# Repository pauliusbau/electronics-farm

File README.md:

# electronics-farm
*All my personal electronics projects goes here..*

### TARDIS Pulsing Light

This is quick and simple TARDIS toy modification based on ATTiny85 uC and a SW-18020P vibration sensor.  More info can be found [here](https://github.com/pauliusbau/electronics-farm/tree/master/TARDIS)

### Flip-Dot Clock

Flip-Dot Clock - a clock made from flip-dot matrix usually used in public buses. Controller is based on ATMega16/32 uC and DS1307 RTC. Clock is also equipped with HC05 Bluetooth module for easy wireless time/date [synchronization](https://github.com/pauliusbau/raspberrypi-mayhem/tree/master/RPI-bluetoothTimeSynch).  

### LEDCtrl - LED Strip Controller

Overly engineered LED strip controller with PIR and LDR sensors based on ATMega8 uC. Firmware allows used to set all of the parameters through LCD menu. Also there is a lot of different working modes.

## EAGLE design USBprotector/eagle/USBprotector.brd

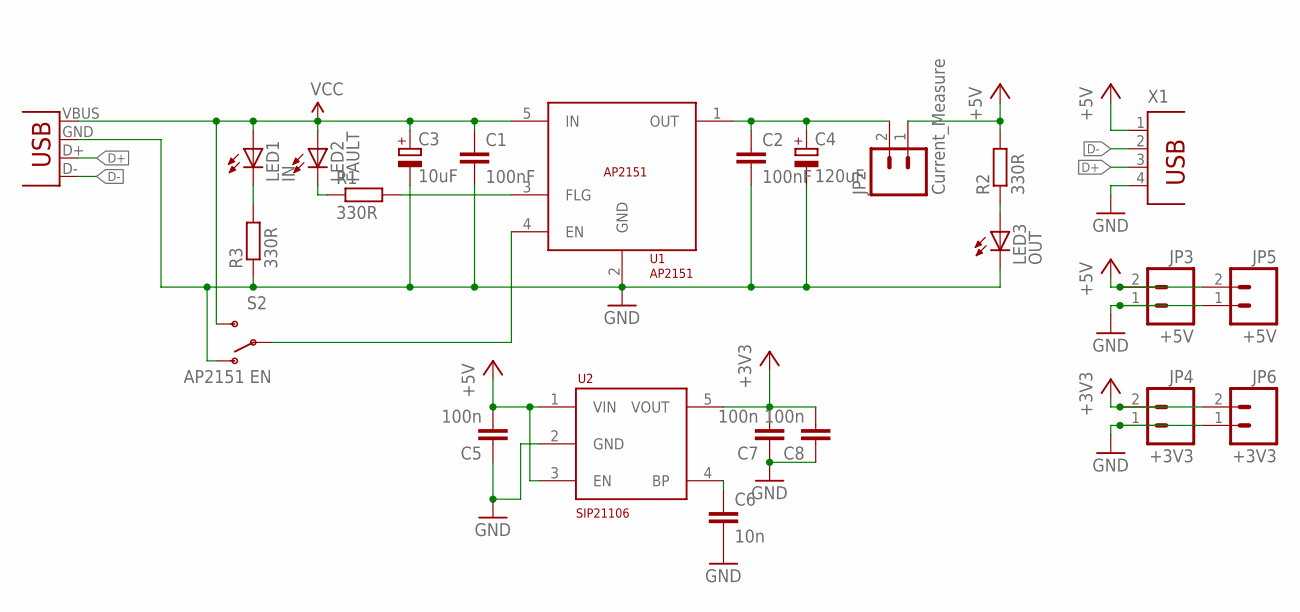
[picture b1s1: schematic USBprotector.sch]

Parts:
C1, C2: 100nF; C0805
C3: 10uF; SMC_C
C4: 120uF; SMC_C
C5, C8: 100n; C0805
C6: 10n; C0805
C7: 100n; C0603
JP1: USB-A-H
JP2: Current_Measure; 1X02
JP3: +5V; SCREWTERMINAL-3.5MM-2
JP4: +3V3; SCREWTERMINAL-3.5MM-2
JP5: +5V; MOLEX-1X2_LOCK
JP6: +3V3; MOLEX-1X2_LOCK
LED1: IN; LED3MM
LED2: FAULT; LED3MM
LED3: OUT; LED3MM
R1, R2, R3: 330R; R1206
S2: AP2151 EN; SWITCH-SPDT
U1: AP2151; SOT23-5
U2: SIP21106; SOT23-5
X1: PN87520

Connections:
5V_OUT: C2.1, C4.+, JP2.2, U1.1 (OUT)
+3V3: C7.2, C8.2, JP4.2, JP6.2, U2.5 (VOUT)
+5V: C5.2, JP2.1, JP3.2, JP5.2, R2.2, U2.1 (VIN), U2.3 (EN), X1.1
D+: JP1.D+ (D-), X1.3
D-: JP1.D- (D+), X1.2
EN: S2.2, U1.4 (EN)
FAULT: R1.2, U1.3 (FLG)
GND: C1.2, C2.2, C3.-, C4.-, C5.1, C6.2, C7.1, C8.1, JP1.GND (VBUS), JP3.1, JP4.1, JP5.1, JP6.1, LED3.K (C), R3.1, S2.1 (O), U1.2 (GND), U2.2 (GND), X1.4
unnamed: LED3.A, R2.1
unnamed: LED2.K (C), R1.1
unnamed: C6.1, U2.4 (BP)
unnamed: LED1.K (C), R3.2
VCC: C1.1, C3.+, JP1.VBUS (GND), LED1.A, LED2.A, S2.3 (S), U1.5 (IN)

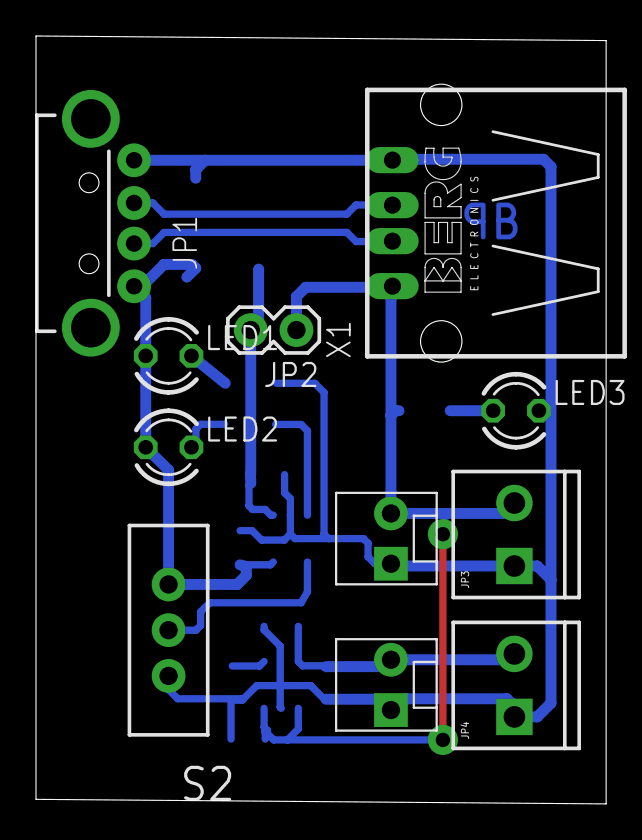
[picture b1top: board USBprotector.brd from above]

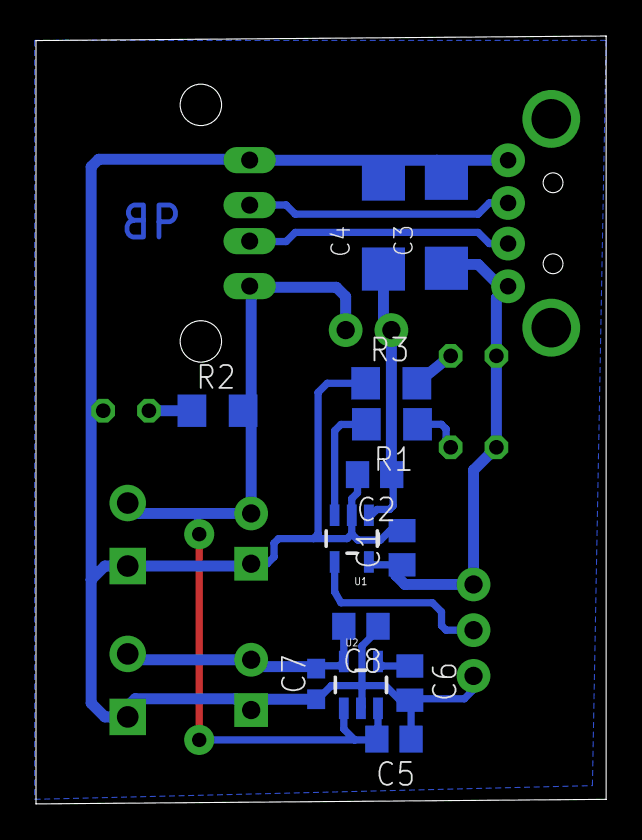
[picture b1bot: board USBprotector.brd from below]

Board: 2 copper layers, 31.7 x 42.7 mm, 24 parts (13 on the bottom side), 13 nets.

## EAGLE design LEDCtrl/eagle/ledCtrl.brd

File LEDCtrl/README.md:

# LEDCtrl - LED strip controller

#### More info and photos can be found in my Lithuanian blog: http://paulius.bautrenas.lt/blog/?p=227

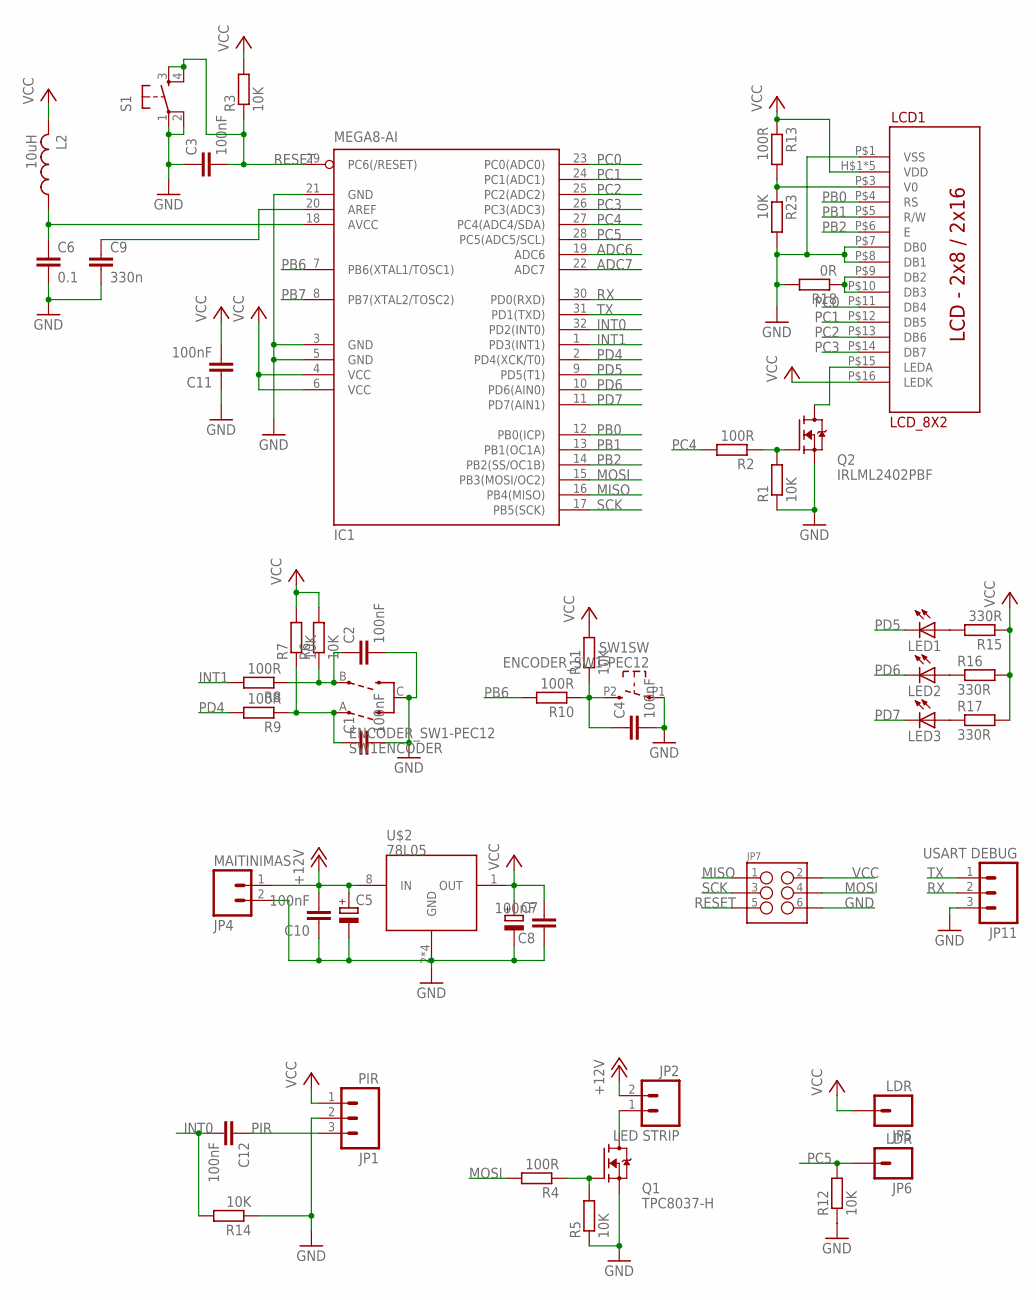
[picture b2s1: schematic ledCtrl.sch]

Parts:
C1, C2, C3, C4, C8, C10, C11, C12: 100nF; C0805
C5, C7: CPOL-EUSMCC; SMC_C
C6: 0.1; C0805K
C9: 330n; C0805
IC1: MEGA8-AI; TQFP32-08
JP1: PIR; 1X03_LOCK
JP2: LED STRIP; SCREWTERMINAL-3.5MM-2-NS
JP4: MAITINIMAS; SCREWTERMINAL-3.5MM-2-NS
JP5, JP6: LDR; 1X01_LONGPAD
JP7: M03X2; 2X3-SHROUDED
JP11: USART DEBUG; 1X03_LOCK
L2: 10uH; L2825P
LCD1: LCD_8X2; LCD_2X8
LED1, LED2, LED3: LEDCHIP-LED0805; CHIP-LED0805
Q1: TPC8037-H; SO8
Q2: IRLML2402PBF; SOT23
R1, R3, R5, R6, R7, R11, R14, R23: 10K; M0805
R2, R4, R8, R9, R10, R13: 100R; M0805
R12: 10K; M1206
R15, R16, R17: 330R; M0805
R18: 0R; M1206
S1: TAC_SWITCHPTH; TACTILE-PTH
SW1: ENCODER_SW1-PEC12; PEC12_INCREMENTAL_ENCODER
U$2: 78L05; SO8

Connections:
+12V: C5.+, C10.2, JP2.2, JP4.1, U$2.8 (IN)
ADC6: IC1.19 (ADC6)
ADC7: IC1.22 (ADC7)
AREF: C9.1, IC1.20 (AREF)
AVCC: C6.1, IC1.18 (AVCC), L2.1
GND: C1.2, C2.2, C3.1, C4.2, C5.-, C6.2, C7.-, C8.1, C9.2, C10.1, C11.1, IC1.3 (GND), IC1.5 (GND), IC1.21 (GND), JP1.2, JP4.2, JP7.6, JP11.3, LCD1.P$1 (VSS), LCD1.P$7 (DB0), LCD1.P$8 (DB1), Q1.1 (S), Q1.2 (S), Q1.3 (S), Q2.2 (S), R1.1, R5.1, R12.1, R14.1, R18.2, R23.2, S1.1, S1.2, SW1.C, SW1.P1 (1), U$2.2 (GND), U$2.3 (GND), U$2.6 (GND), U$2.7 (GND)
INT0: C12.2, IC1.32 (PD2(INT0)), R14.2
INT1: IC1.1 (PD3(INT1)), R8.2
MISO: IC1.16 (PB4(MISO)), JP7.1
MOSI: IC1.15 (PB3(MOSI/OC2)), JP7.4, R4.2
unnamed: JP2.1, Q1.5 (D), Q1.6 (D), Q1.7 (D), Q1.8 (D)
unnamed: LED1.A, R15.2
unnamed: C2.1, R6.1, R8.1, SW1.B
unnamed: C1.1, R7.1, R9.1, SW1.A
unnamed: LED2.A, R16.1
unnamed: LED3.A, R17.1
unnamed: LCD1.P$15 (LEDA), Q2.3 (D)
unnamed: Q2.1 (G), R1.2, R2.1
unnamed: Q1.4 (G), R4.1, R5.2
unnamed: C4.1, R10.1, R11.1, SW1.P2 (2)
unnamed: LCD1.P$9 (DB2), LCD1.P$10 (DB3), R18.1
unnamed: LCD1.P$3 (V0), R13.2, R23.1
PB0: IC1.12 (PB0(ICP)), LCD1.P$4 (RS)
PB1: IC1.13 (PB1(OC1A)), LCD1.P$5 (R/W)
PB2: IC1.14 (PB2(SS/OC1B)), LCD1.P$6 (E)
PB6: IC1.7 (PB6(XTAL1/TOSC1)), R10.2
PB7: IC1.8 (PB7(XTAL2/TOSC2))
PC0: IC1.23 (PC0(ADC0)), LCD1.P$11 (DB4)
PC1: IC1.24 (PC1(ADC1)), LCD1.P$12 (DB5)
PC2: IC1.25 (PC2(ADC2)), LCD1.P$13 (DB6)
PC3: IC1.26 (PC3(ADC3)), LCD1.P$14 (DB7)
PC4: IC1.27 (PC4(ADC4/SDA)), R2.2
PC5: IC1.28 (PC5(ADC5/SCL)), JP6.1, R12.2
PD4: IC1.2 (PD4(XCK/T0)), R9.2
PD5: IC1.9 (PD5(T1)), LED1.C
PD6: IC1.10 (PD6(AIN0)), LED2.C
PD7: IC1.11 (PD7(AIN1)), LED3.C
PIR: C12.1, JP1.3
RESET: C3.2, IC1.29 (PC6(/RESET)), JP7.5, R3.1, S1.3, S1.4
RX: IC1.30 (PD0(RXD)), JP11.2
SCK: IC1.17 (PB5(SCK)), JP7.3
TX: IC1.31 (PD1(TXD)), JP11.1
VCC: C7.+, C8.2, C11.2, IC1.4 (VCC), IC1.6 (VCC), JP1.1, JP5.1, JP7.2, L2.2, LCD1.H$1 (VDD), LCD1.H$2 (VDD), LCD1.H$3 (VDD), LCD1.H$4 (VDD), LCD1.P$2 (VDD), LCD1.P$16 (LEDK), R3.2, R6.2, R7.2, R11.2, R13.1, R15.1, R16.2, R17.2, U$2.1 (OUT)

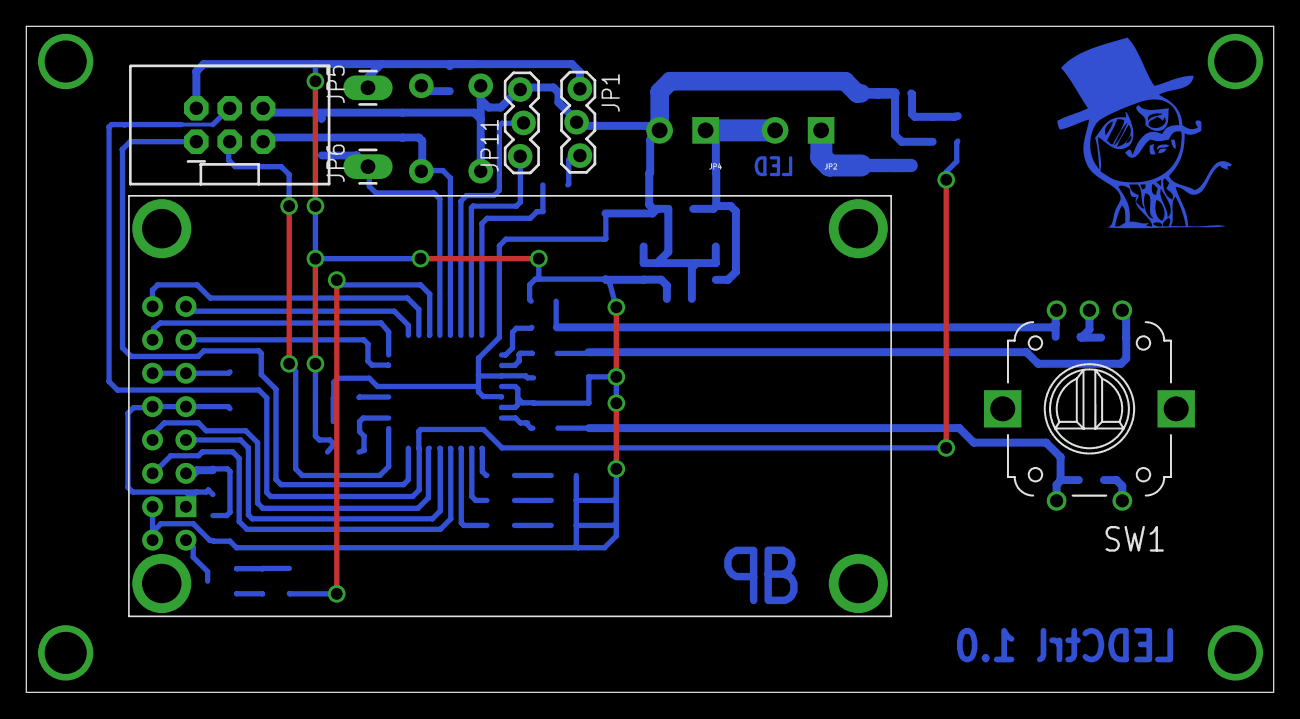
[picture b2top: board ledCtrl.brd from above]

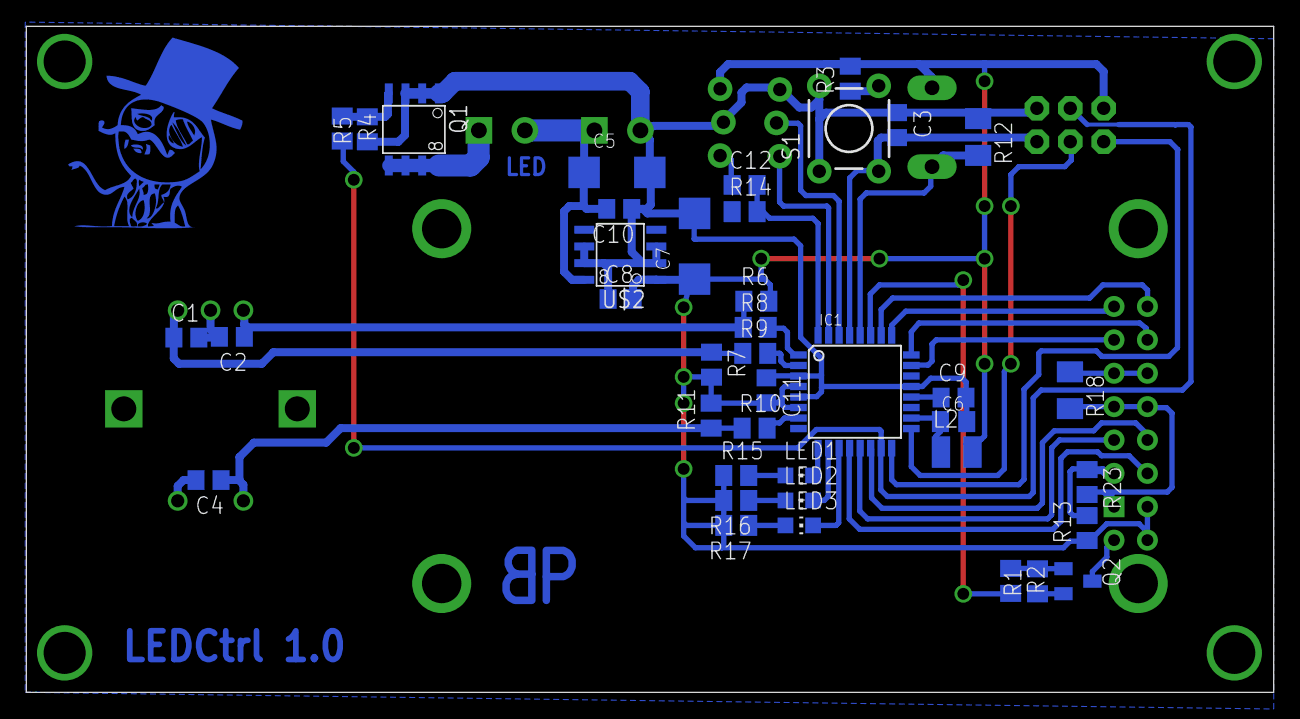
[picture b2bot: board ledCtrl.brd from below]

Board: 2 copper layers, 94.9 x 50.7 mm, 50 parts (40 on the bottom side), 40 nets.

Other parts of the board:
U$3: TROLIS6

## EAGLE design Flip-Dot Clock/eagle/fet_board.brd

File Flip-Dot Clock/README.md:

# Flip-Dot Clock

Clock is based on a custom flip-dot controller equipped with DS1307 RTC. 
##### More info and photos can be found here: https://hackaday.io/project/168888-flip-dot-clock

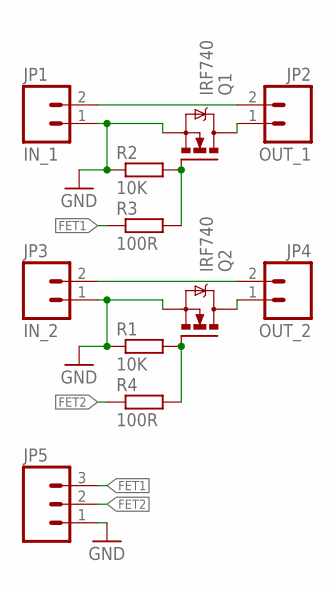
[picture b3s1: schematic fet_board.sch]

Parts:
JP1: IN_1; SCREWTERMINAL-3.5MM-2-NS
JP2: OUT_1; SCREWTERMINAL-3.5MM-2-NS
JP3: IN_2; SCREWTERMINAL-3.5MM-2-NS
JP4: OUT_2; SCREWTERMINAL-3.5MM-2-NS
JP5: M03POLAR_LOCK; MOLEX-1X3_LOCK
Q1, Q2: IRF740; TO220BV
R1, R2: 10K; R0805
R3, R4: 100R; R0805

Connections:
FET1: JP5.3, R3.1
FET2: JP5.2, R4.1
GND: JP1.1, JP3.1, JP5.1, Q1.S, Q2.S, R1.1, R2.1
unnamed: JP2.1, Q1.D
unnamed: Q1.G, R2.2, R3.2
unnamed: JP4.1, Q2.D
unnamed: Q2.G, R1.2, R4.2
POWER1: JP1.2, JP2.2
POWER2: JP3.2, JP4.2

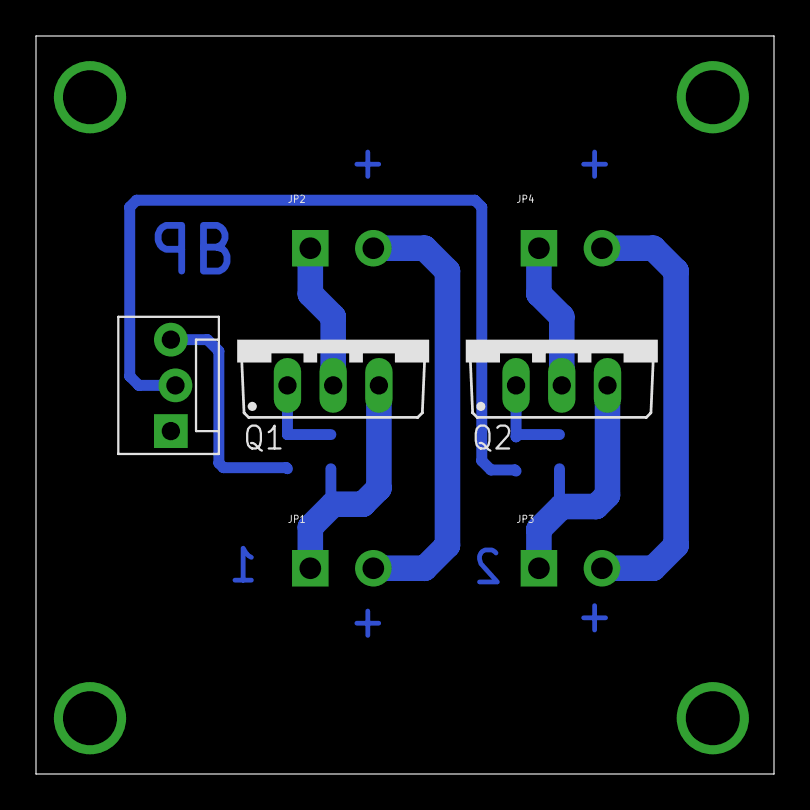
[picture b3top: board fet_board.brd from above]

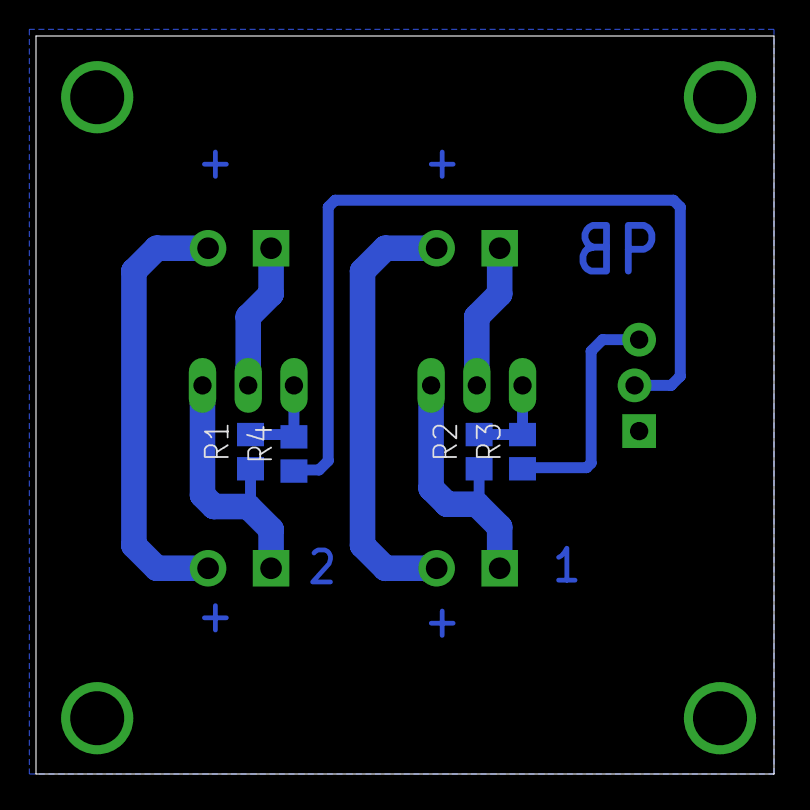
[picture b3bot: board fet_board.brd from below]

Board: 2 copper layers, 41.0 x 41.0 mm, 11 parts (4 on the bottom side), 9 nets.

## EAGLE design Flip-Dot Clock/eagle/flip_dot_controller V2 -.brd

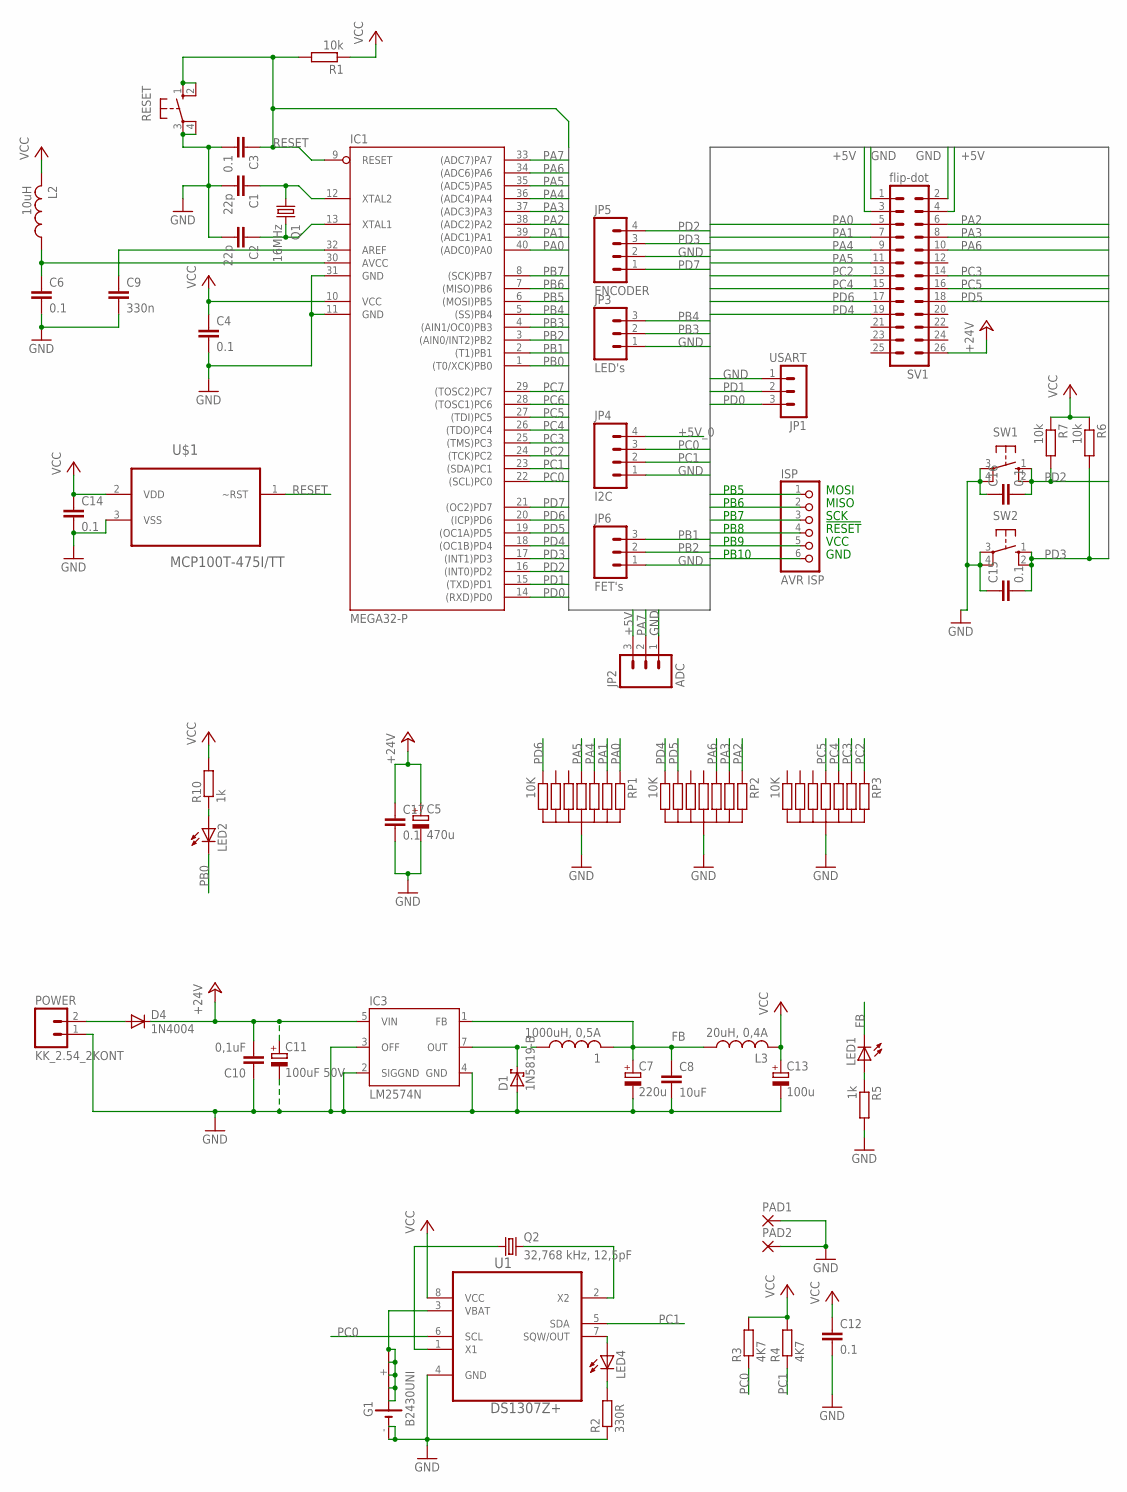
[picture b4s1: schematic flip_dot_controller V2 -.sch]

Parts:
1: 1000uH, 0,5A; RITE
C1, C2: 22p; C0805
C3, C12, C17: 0.1; C0805
C4, C6, C14, C15, C16: 0.1; C0805K
C5: 470u; E5-10,5
C7: 220u; E5-8,5
C8: 10uF; C0805
C9: 330n; C0805
C10: 0,1uF; C0805K
C11: 100uF 50V; E5-10,5
C13: 100u; E5-8,5
D1: 1N5819-B; DO41-7.6
D4: 1N4004; DO41-10
G1: B2430UNI
IC1: MEGA32-P; DIL40
IC3: LM2574N; DIL-08
ISP: AVR ISP; 1X06
JP1: USART; MA03-1
JP2: ADC; 1X03_LOCK
JP3: LED's; 1X03_LOCK
JP4: I2C; 1X04_LOCK
JP5: ENCODER; 1X04_LOCK
JP6: FET's; 1X03_LOCK
L2: 10uH; 0207/5V
L3: 20uH, 0,4A; 0207/5V
LED1, LED2, LED4: LED3MM
PAD1, PAD2: 2,15/1,0
POWER: KK_2.54_2KONT; KONTAKTINE_KALADELE_2.54_2KONT
Q1: 16MHz; HC49/S
Q2: 32,768 kHz, 12,5pF; TC38H
R1, R6, R7: 10k; R0805
R2: 330R; R0805
R3, R4: 4K7; R0805
R5, R10: 1k; R0805
RESET: 10-XX; B3F-10XX
RP1, RP2, RP3: 10K; 1X8_RES_PACK
SV1: flip-dot; 3M_26
SW1, SW2: 10-XX; B3F-10XX
U1: DS1307Z+; SOIC127P600X175-8N
U$1: MCP100T-475I/TT; SOT95P237X112-3N

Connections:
+5V: C4.1, C12.1, C13.+, C14.1, IC1.10 (VCC), ISP.5, JP2.3, L2.2, L3.2, R1.1, R3.2, R4.2, R6.1, R7.1, R10.2, SV1.3, SV1.4, U1.8 (VCC), U$1.2 (VDD)
+5V_0: JP4.4
+24V: C5.+, C10.2, C11.+, C17.1, D4.C, IC3.5 (VIN), SV1.26
FB: 1.2, C7.+, C8.1, IC3.1 (FB), L3.1, LED1.K (C)
GND: C1.2, C2.2, C3.2, C4.2, C5.-, C6.2, C7.-, C8.2, C9.2, C10.1, C11.-, C12.2, C13.-, C14.2, C15.1, C16.1, C17.2, D1.A, G1.-, G1.-@1 (-), IC1.11 (GND), IC1.31 (GND), IC3.2 (SIGGND), IC3.3 (OFF), IC3.4 (GND), ISP.6, JP1.1, JP2.1, JP3.1, JP4.1, JP5.2, JP6.1, PAD1.1, PAD2.1, POWER.1, R2.1, R5.2, RESET.3, RESET.4 (P1), RP1.1, RP2.1, RP3.1, SV1.1, SV1.2, SW1.3, SW1.4 (P1), SW2.3, SW2.4 (P1), U1.4 (GND), U$1.3 (VSS)
unnamed: C2.1, IC1.13 (XTAL1), Q1.2
unnamed: C1.1, IC1.12 (XTAL2), Q1.1
unnamed: C9.1, IC1.32 (AREF)
unnamed: C6.1, IC1.30 (AVCC), L2.1
unnamed: Q2.1, U1.1 (X1)
unnamed: D4.A, POWER.2
unnamed: Q2.2, U1.2 (X2)
unnamed: LED4.A, U1.7 (SQW/OUT)
unnamed: LED4.K (C), R2.2
unnamed: LED1.A, R5.1
unnamed: LED2.A, R10.1
OUT: 1.1, D1.C, IC3.7 (OUT)
PA0: IC1.40 ((ADC0)PA0), RP1.2, SV1.5
PA1: IC1.39 ((ADC1)PA1), RP1.3, SV1.7
PA2: IC1.38 ((ADC2)PA2), RP2.2, SV1.6
PA3: IC1.37 ((ADC3)PA3), RP2.3, SV1.8
PA4: IC1.36 ((ADC4)PA4), RP1.4, SV1.9
PA5: IC1.35 ((ADC5)PA5), RP1.5, SV1.11
PA6: IC1.34 ((ADC6)PA6), RP2.4, SV1.10
PA7: IC1.33 ((ADC7)PA7), JP2.2
PB0: IC1.1 ((T0/XCK)PB0), LED2.K (C)
PB1: IC1.2 ((T1)PB1), JP6.3
PB2: IC1.3 ((AIN0/INT2)PB2), JP6.2
PB3: IC1.4 ((AIN1/OC0)PB3), JP3.2
PB4: IC1.5 ((SS)PB4), JP3.3
PB5: IC1.6 ((MOSI)PB5), ISP.1
PB6: IC1.7 ((MISO)PB6), ISP.2
PB7: IC1.8 ((SCK)PB7), ISP.3
PC0: IC1.22 ((SCL)PC0), JP4.3, R3.1, U1.6 (SCL)
PC1: IC1.23 ((SDA)PC1), JP4.2, R4.1, U1.5 (SDA)
PC2: IC1.24 ((TCK)PC2), RP3.2, SV1.13
PC3: IC1.25 ((TMS)PC3), RP3.3, SV1.14
PC4: IC1.26 ((TDO)PC4), RP3.4, SV1.15
PC5: IC1.27 ((TDI)PC5), RP3.5, SV1.16
PC6: IC1.28 ((TOSC1)PC6)
PC7: IC1.29 ((TOSC2)PC7)
PD0: IC1.14 ((RXD)PD0), JP1.3
PD1: IC1.15 ((TXD)PD1), JP1.2
PD2: C16.2, IC1.16 ((INT0)PD2), JP5.4, R7.2, SW1.1 (S), SW1.2 (S1)
PD3: C15.2, IC1.17 ((INT1)PD3), JP5.3, R6.2, SW2.1 (S), SW2.2 (S1)
PD4: IC1.18 ((OC1B)PD4), RP2.8, SV1.19
PD5: IC1.19 ((OC1A)PD5), RP2.7, SV1.18
PD6: IC1.20 ((ICP)PD6), RP1.8, SV1.17
PD7: IC1.21 ((OC2)PD7), JP5.1
RESET: C3.1, IC1.9 (RESET), ISP.4, R1.2, RESET.1 (S), RESET.2 (S1), U$1.1 (~RST)
VBAT: G1.+, G1.+@1 (+), G1.+@2 (+), G1.+@3 (+), G1.+@4 (+), U1.3 (VBAT)

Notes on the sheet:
MOSI
MISO
SCK
!RESET
VCC
GND
PB6
PB7
PB8
PB9
PB10
PB5

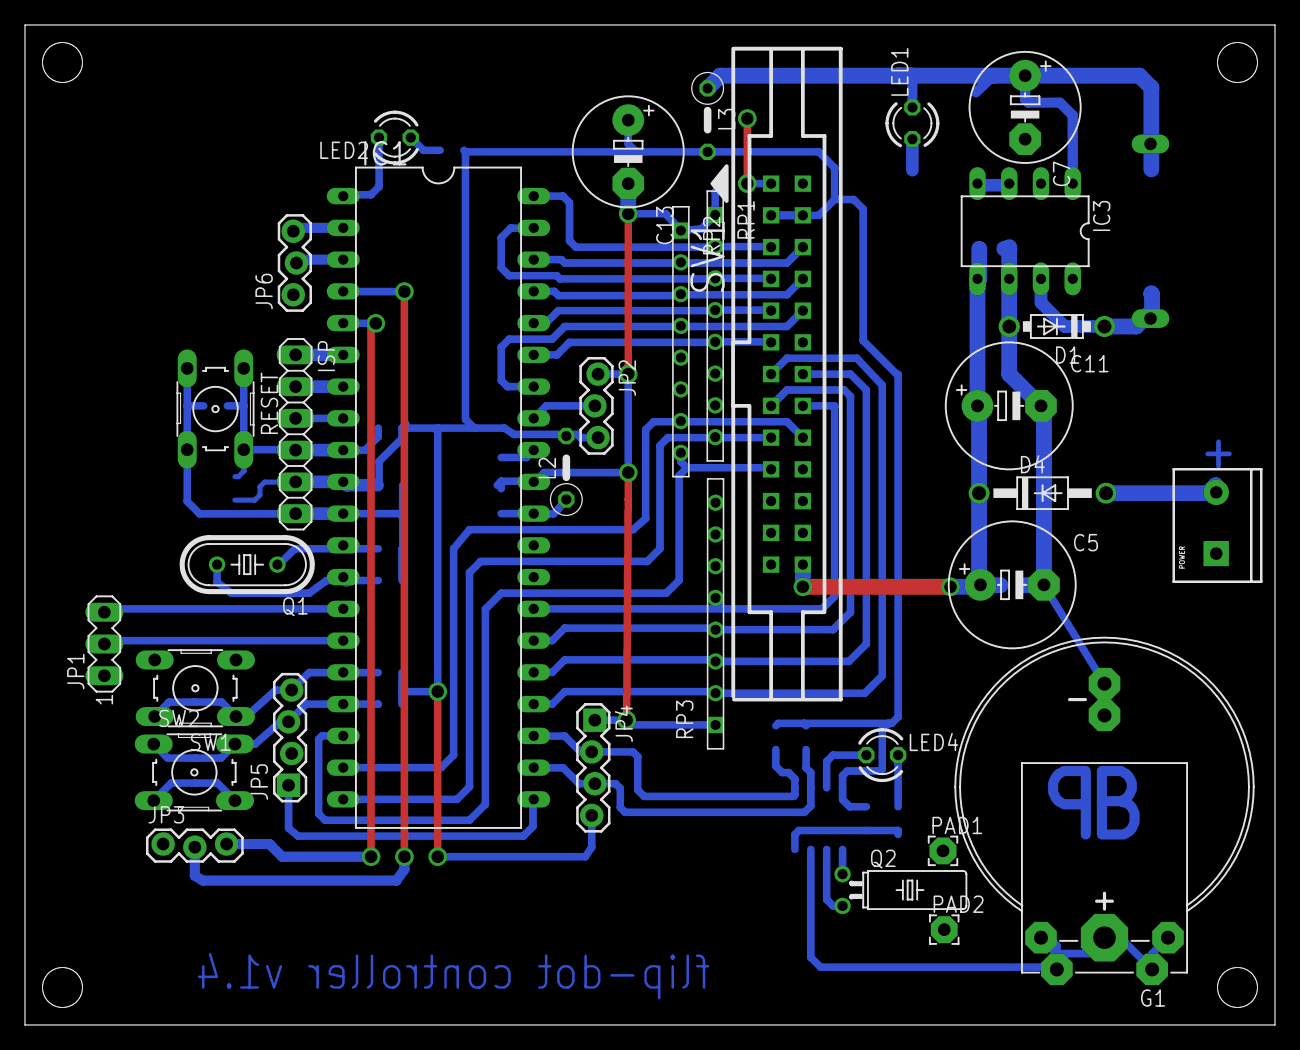
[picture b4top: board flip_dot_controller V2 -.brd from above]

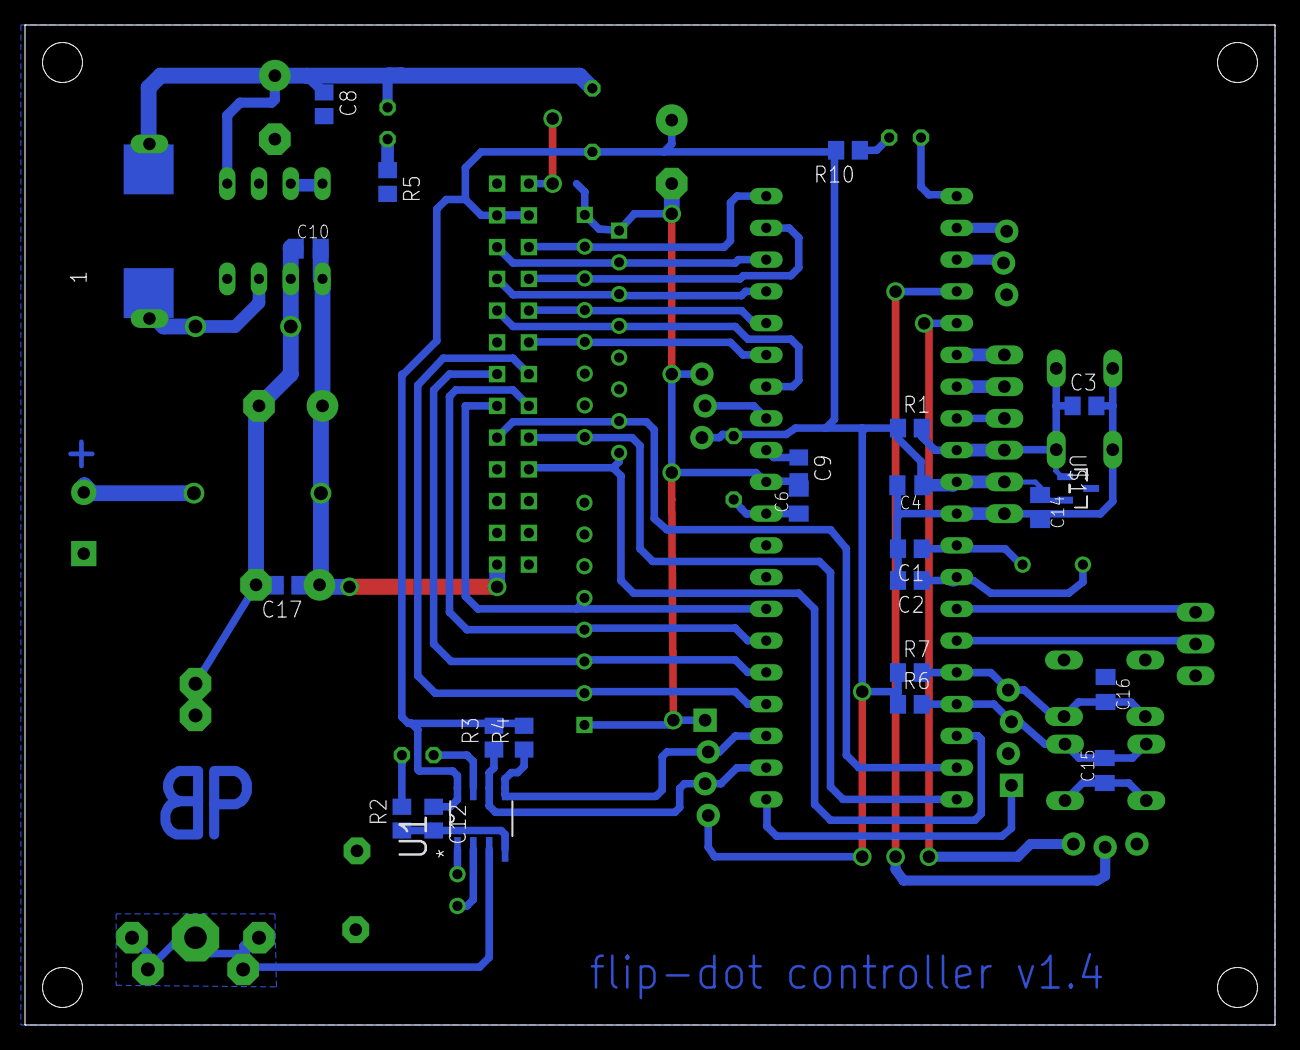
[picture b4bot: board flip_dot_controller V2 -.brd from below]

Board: 2 copper layers, 100.0 x 80.0 mm, 57 parts (24 on the bottom side), 48 nets.

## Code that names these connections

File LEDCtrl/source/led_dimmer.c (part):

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
#define BUTTON_PORT PORTC
#define BUTTON_PIN	PINC
#define BUTTON_BIT 	PC0

#define LCD_LED_PORT PORTC
#define LCD_LED_PIN	PINC
#define LCD_LED_BIT PC4

#define LED_PORT PORTD
#define LED_PIN	PIND
#define LED1_BIT PD5
#define LED2_BIT PD6
#define LED3_BIT PD7


//------------ config kintamieji ------------
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volatile char 	config = 0; 	// 0 - nieko; 1 - configo puslapiai; 2 - 2as configo lygis

volatile char 	meniu_mode = 0; //0 - nieko; 1 - ijungi AlwaysON; 2 - ijungi PIRMode; 3 - PIRMode nustatymai 
volatile char 	work_mode = 0; //0 - LED Off; 1 - AlwaysON; 2 - PIR mode; 3 - PIR/ADC mode

volatile char 	menu_page = 0;
static char 	menu_page_max=5; //number of menu pages
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volatile unsigned char 	LDRn=0;
volatile unsigned char 	LDRn0=0; //0 - neinvertuotas, 1 - invertuotas LDR

volatile unsigned char  PIR=0; //ar suveike PIR: 0 - ne;  1 - suveike PIR pertrauktis
volatile unsigned char  LDRthISR=0; //1 - kai yra tamsu ir buvo pagal LDR buvo ijugta PIR pertrauktis, 0 - pakankamai sviesu 


static unsigned char fadein[]={0, 1, 2, 3, 5, 8, 11, 15, 20, 25, 30, 36, 43, 49, 56, 64, 72, 80, 88, 97, 105, 114, 123, 132, 141, 150, 158, 167, 175, 183, 191, 199, 206, 212, 219, 225, 230, 235, 240, 244, 247, 250, 252, 253, 254, 255};
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

	fade_in();
	PIR=1; //nuo cia visa darba atlieka TIMER1 pertrauktis

	
	//start_timer1();
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	//--------PWM nustatymai ------------ 
	//buvo {OCR2=OCR2+0x05;} else {OCR2=OCR2-0x05;}
	nuostatas=nuostato_radimas(OCR2); 
	if(bit_is_set(PIND, PD4)) {if (nuostatas!=(sizeof(fadein)/sizeof(fadein[0])-1))
												nuostatas++; else nuostatas=0;} 												
	else {if(nuostatas==0) nuostatas=(sizeof(fadein)/sizeof(fadein[0])-1); else nuostatas--;}		
											
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

	//--------- LDR->PWM konvertavimo koeficineto (LDRkoef) nustatymas -----
	if(bit_is_set(PIND, PD4)) 
		{if (LDRkoef!=25) LDRkoef++; else LDRkoef=0;} 
	else {if (LDRkoef==0) LDRkoef=25; else LDRkoef--;}

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			clock_second=0; 
		//	GICR|=_BV(INT0); //ijungiam PIR pertraukti	
		//	stop_timer1();
			PIR=0;
			show_work_mode();
			fade_out();	 
			}
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	LCD_LED_PORT |= _BV(LCD_LED_BIT); //ijungiam LCD pasvietimas

	//USART
	DDRD|=_BV(PD1); //TX
	PORTD|=_BV(PD1);
	DDRD&=~_BV(PD0); //RX

	//ROT ENCODER
	DDRD&=~_BV(PD3); //INT1 
	PORTD|=_BV(PD3);
	DDRD&=~_BV(PD4); 
	PORTD|=_BV(PD4);
	//ROT ENCODER BUTTON
	DDRB&=~_BV(PB6); 
	PORTB|=_BV(PB6);


	//PIR
	DDRD&=~_BV(PD2); //INT0
//	PORTD|=_BV(PD2);

	//PWM OUT
	DDRB|=_BV(PB3); 
 
	//----------------- initai -----------------------------

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
//-------------------- to go into main menu 00--------------------

//		if (bit_is_clear(PINB, PB6)){	
//		lcd_light=1;
//		}
		
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				}
				
				else if (menu_page==1){		//PIR meniu punktas
				work_mode=2;				//PIR - wmode
				EEPROM_write(25, work_mode);
				meniu=0;
				show_work_mode();
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				}				

				else if (menu_page==2){		//PIR/LDR meniu punktas
				work_mode=3;				//PIR/LDR - wmode
				EEPROM_write(25, work_mode);
				meniu=0;
				show_work_mode();
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
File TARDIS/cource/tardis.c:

#include <avr/io.h>
#include <util/delay.h>
#include <stdio.h>
#include <avr/interrupt.h>
#include <avr/pgmspace.h>
#include <avr/sleep.h> 

#define F_CPU 8000000UL	

static char tardis[]={0,0,2,5,10,16,24,33,43,54,67,80,94,109,124,139,154,168,182,195,208,219,229,237,244,250,253,255};
static char tardis_count = 3;

void fade_in(){
	for (char i=0;i<(sizeof(tardis)/sizeof(tardis[0]));i++){
	_delay_ms(30);
	OCR0B = tardis[i];
	}
}

void fade_out(){
	for (char i=(sizeof(tardis)/sizeof(tardis[0]))-1;i>0;i--){
	OCR0B = tardis[i];
	_delay_ms(30);
	}
}

void tardis_light(){
	for(char i=0; i<tardis_count;i++){
		fade_in();
		_delay_ms(250);
		fade_out();
	
		_delay_ms(250);
	}
}

void go_to_sleep(){
 	 cli();
	 set_sleep_mode(SLEEP_MODE_PWR_DOWN); 
	 sleep_enable();
     sei();
	 sleep_cpu();
	 sleep_disable();
     //sei();	
}


ISR(INT0_vect){
	
	cli();

	tardis_light();

	sei();

	_delay_ms(100);
	go_to_sleep();
}


int main(){

	//Status LED
	DDRB |= (1<<PB4);
	PORTB &= ~_BV(PB4); 

	//Main LED
	DDRB |= (1<<PB1);  // make OC0B PWM output pin

	//PWM
	TCCR0A = (1<<COM0B1)|(1<<WGM00);  // mode #1
	TCCR0B = (1<<CS00);  // clkI/O/(No prescaling)


	//INT0 enable:
	MCUCR&=~(_BV(ISC01)) | ~(_BV(ISC00));
	GIMSK|=_BV(INT0);

	//PB2 as input for INT0
	DDRB &=~_BV(PB2);
	PORTB |= (1<<PB2);
	
	sei();

	//Disable ADC, saves ~230uA
	ADCSRA &= ~(1<<ADEN);
	
	
	tardis_light();
	
	

	go_to_sleep();

		

	while(5){

			
	}

}

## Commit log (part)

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2015-07-01 First upload
2015-07-01 cleaning up
2015-07-01 more pictures
2015-07-31 1st commit of an old project
    http://paulius.bautrenas.lt/blog/?p=607
2015-07-31 1st commit
    http://paulius.bautrenas.lt/blog/?p=227
2015-07-31 images!
2015-10-22 just image size change
2016-07-28 Learning ARM stuff on STM32F446 Nucleo-64 board. Did External Interrupt and UART DMA demo..
2016-07-29 Running FreeRTOS on a STM32Nucleo64 STM32F446 Code ideas from https://github.com/cnoviello/stm32-nucleof4/blob/master/stm32-nucleof4-freertos/src/main.c (http://www.carminenoviello.com/2015/06/22/run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
2017-01-02 USBprotector schematics and pcb
2017-01-29 first! (keil version)
2017-01-29 turning on LED2 and LED3. Blinking LED3
2017-01-29 ISR: adding user_bnt_pin interrupt to toggle led2_pin
2017-01-29 ignoring keil garbage
2017-01-29 a little bit of garbage
2017-01-29 USART
2017-02-04 pajaudojau LED1
2017-02-04 panaudojau LED1
2017-02-04 usart experiments
2017-02-05 šviesos diodų pamirksėjimai ir mygtuko tikrinimas while cikle (laborams)
2017-02-08 moved nucleo-64 stuff to another folder
2017-02-12 apsivalymas nuo LD1 reikalų
2017-03-04 PWM & User Btn double click
2017-03-29 nieko rimto
2017-04-03 ingoruojam
2024-04-01 Staircase Lamp

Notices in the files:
parts and their libraries:
SparkFun-Connectors: Licensing: Creative Commons ShareAlike 4.0 International - https://creativecommons.org/licenses/by-sa/4.0
SparkFun-Electromechanical: Licensing: CC v3.0 Share-Alike You are welcome to use this library for commercial purposes.
